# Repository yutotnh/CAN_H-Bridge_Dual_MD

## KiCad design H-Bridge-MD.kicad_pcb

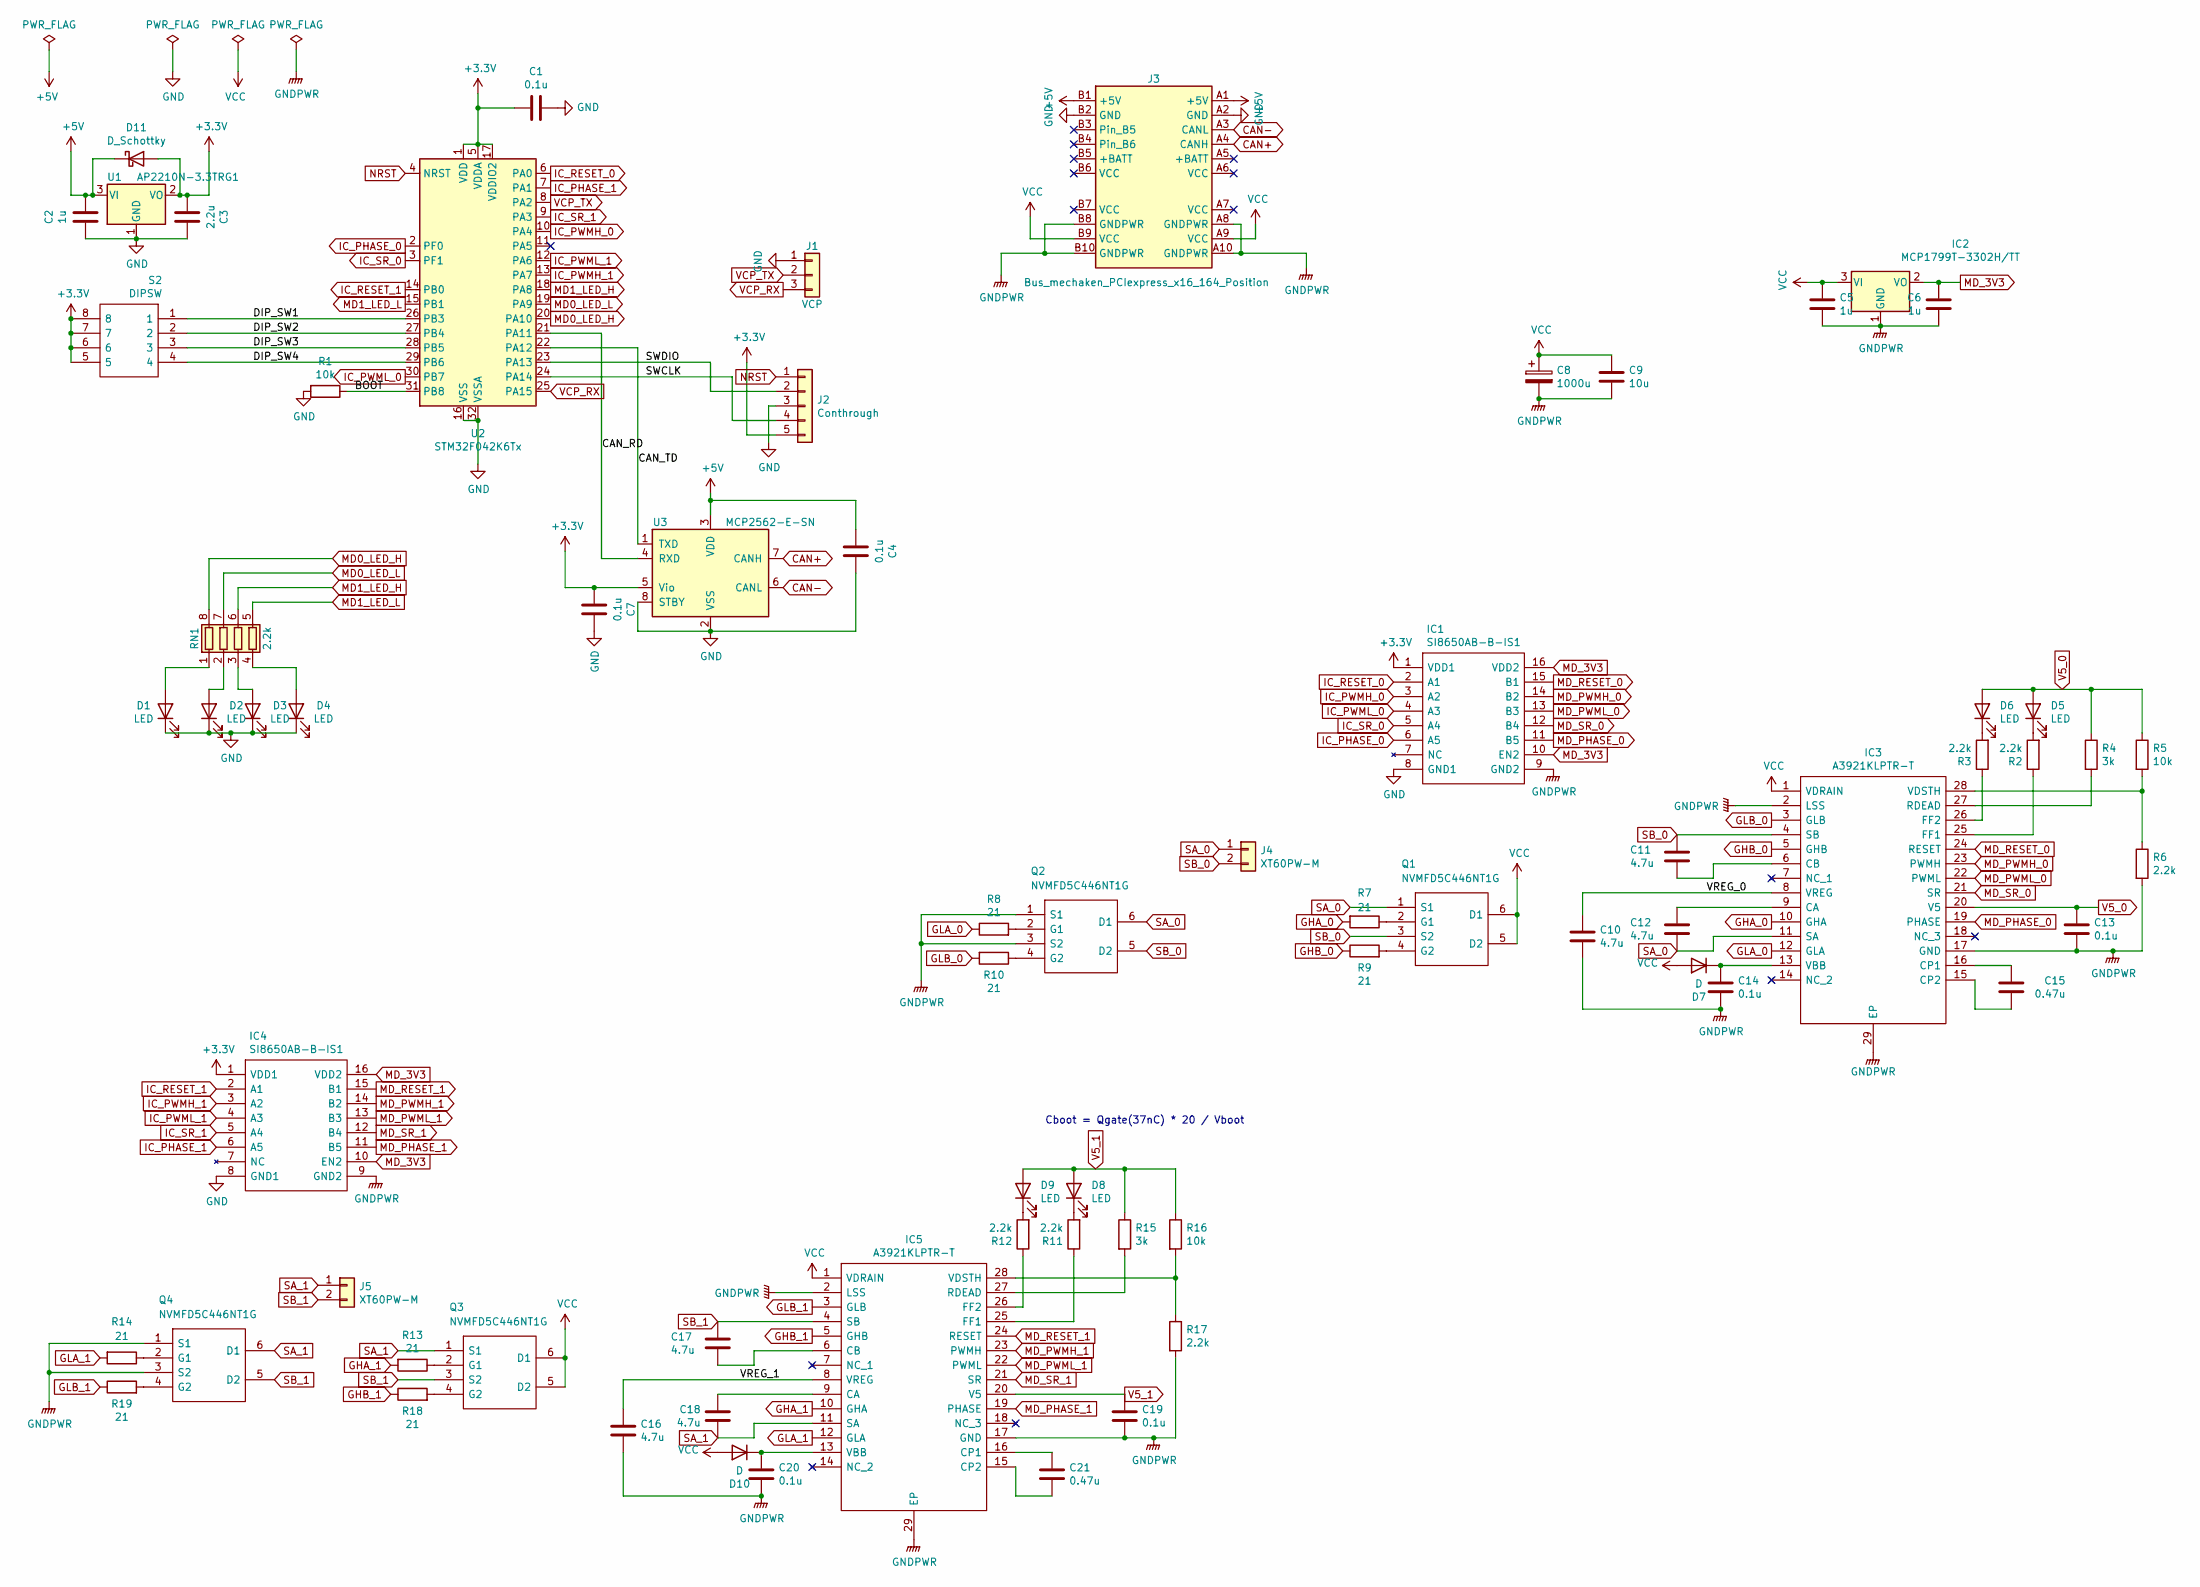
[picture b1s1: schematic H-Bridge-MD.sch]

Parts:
C1, C4, C7, C13, C14, C19, C20: 0.1u; C_0805_2012Metric
C2, C5, C6: 1u; C_0805_2012Metric
C3: 2.2u; C_0805_2012Metric
C8: 1000u; PinSocket_1x02_P2.54mm_Vertical
C9: 10u; C_0805_2012Metric
C10, C11, C12, C16, C17, C18: 4.7u; C_0805_2012Metric
C15, C21: 0.47u; C_0805_2012Metric
D1, D2, D3, D4, D5, D6, D8, D9: LED; LED_0603_1608Metric_Castellated
D7, D10: D; D_0603_1608Metric
D11: D_Schottky; D_0603_1608Metric
IC1, IC4: SI8650AB-B-IS1; SOIC127P600X175-16N; Mouser Part Number 634-SI8650AB-B-IS1
IC2: MCP1799T-3302H/TT; SOT-23_Handsoldering; Manufacturer_Part_Number MCP1799T-3302H/TT
IC3, IC5: A3921KLPTR-T; SOP65P640X120-29N; Manufacturer_Part_Number A3921KLPTR-T
J1: VCP; PinHeader_1x03_P2.54mm_Vertical
J2: Conthrough; PinHeader_1x05_P2.54mm_Vertical
J3: Bus_mechaken_PCIexpress_x16_164_Position; BUS_mechaken_PCIexpress_x16
J4, J5: XT60PW-M; XT60PW
Q1, Q2, Q3, Q4: NVMFD5C446NT1G; NVMFD5C446NLWFT1G; Mouser Part Number 863-NVMFD5C446NT1G
R1, R5, R16: 10k; R_0603_1608Metric
R2, R3, R6, R11, R12, R17: 2.2k; R_0603_1608Metric
R4, R15: 3k; R_0603_1608Metric
R7, R8, R9, R10, R13, R14, R18, R19: 21; R_0603_1608Metric
RN1: 2.2k; R_Array_Convex_4x1206
S2: DIPSW; SW_DIP_SPSTx04_Slide_9.78x12.34mm_W7.62mm_P2.54mm; Manufacturer_Part_Number IKD0403101
U1: AP2210N-3.3TRG1; SOT-23W_Handsoldering
U2: STM32F042K6Tx; LQFP-32_7x7mm_P0.8mm
U3: MCP2562-E-SN; SOIC-8_3.9x4.9mm_P1.27mm

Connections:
+3V3: C1.2, C3.2, C7.2, D11.2 (A), IC1.1 (VDD1), IC4.1 (VDD1), J2.5, S2.5, S2.6, S2.7, S2.8, U1.2 (VO), U2.1 (VDD), U2.5 (VDDA), U2.17 (VDDIO2), U3.5 (Vio)
+5V: C2.1, C4.2, D11.1 (K), J3.A1 (+5V), J3.B1 (+5V), U1.3 (VI), U3.3 (VDD)
/BOOT: R1.1, U2.31 (PB8)
/CAN_RD: U2.21 (PA11), U3.4 (RXD)
/CAN_TD: U2.22 (PA12), U3.1 (TXD)
/DIP_SW1: S2.1, U2.26 (PB3)
/DIP_SW2: S2.2, U2.27 (PB4)
/DIP_SW3: S2.3, U2.28 (PB5)
/DIP_SW4: S2.4, U2.29 (PB6)
/SWCLK: J2.4, U2.24 (PA14)
/SWDIO: J2.2, U2.23 (PA13)
/VREG_0: C10.1, IC3.8 (VREG)
/VREG_1: C16.1, IC5.8 (VREG)
CAN+: J3.A4 (CANH), U3.7 (CANH)
CAN-: J3.A3 (CANL), U3.6 (CANL)
GHA_0: IC3.10 (GHA), R7.2
GHA_1: IC5.10 (GHA), R13.2
GHB_0: IC3.5 (GHB), R9.1
GHB_1: IC5.5 (GHB), R18.1
GLA_0: IC3.12 (GLA), R8.1
GLA_1: IC5.12 (GLA), R14.2
GLB_0: IC3.3 (GLB), R10.2
GLB_1: IC5.3 (GLB), R19.1
GND: C1.1, C2.2, C3.1, C4.1, C7.1, D1.1 (K), D2.1 (K), D3.1 (K), D4.1 (K), IC1.8 (GND1), IC4.8 (GND1), J1.1, J2.3, J3.A2 (GND), J3.B2 (GND), R1.2, U1.1 (GND), U2.16 (VSS), U2.32 (VSSA), U3.2 (VSS), U3.8 (STBY)
GNDPWR: C5.2, C6.1, C8.2, C9.2, C10.2, C13.2, C14.2, C16.2, C19.2, C20.2, IC1.9 (GND2), IC2.1 (GND), IC3.2 (LSS), IC3.17 (GND), IC3.29 (EP), IC4.9 (GND2), IC5.2 (LSS), IC5.17 (GND), IC5.29 (EP), J3.A8 (GNDPWR), J3.A10 (GNDPWR), J3.B8 (GNDPWR), J3.B10 (GNDPWR), Q2.1 (S1), Q2.3 (S2), Q4.1 (S1), Q4.3 (S2), R6.2, R17.2
IC_PHASE_0: IC1.6 (A5), U2.2 (PF0)
IC_PHASE_1: IC4.6 (A5), U2.7 (PA1)
IC_PWMH_0: IC1.3 (A2), U2.10 (PA4)
IC_PWMH_1: IC4.3 (A2), U2.13 (PA7)
IC_PWML_0: IC1.4 (A3), U2.30 (PB7)
IC_PWML_1: IC4.4 (A3), U2.12 (PA6)
IC_RESET_0: IC1.2 (A1), U2.6 (PA0)
IC_RESET_1: IC4.2 (A1), U2.14 (PB0)
IC_SR_0: IC1.5 (A4), U2.3 (PF1)
IC_SR_1: IC4.5 (A4), U2.9 (PA3)
MD0_LED_H: RN1.8 (R1.2), U2.20 (PA10)
MD0_LED_L: RN1.7 (R2.2), U2.19 (PA9)
MD1_LED_H: RN1.6 (R3.2), U2.18 (PA8)
MD1_LED_L: RN1.5 (R4.2), U2.15 (PB1)
MD_3V3: C6.2, IC1.10 (EN2), IC1.16 (VDD2), IC2.2 (VO), IC4.10 (EN2), IC4.16 (VDD2)
MD_PHASE_0: IC1.11 (B5), IC3.19 (PHASE)
MD_PHASE_1: IC4.11 (B5), IC5.19 (PHASE)
MD_PWMH_0: IC1.14 (B2), IC3.23 (PWMH)
MD_PWMH_1: IC4.14 (B2), IC5.23 (PWMH)
MD_PWML_0: IC1.13 (B3), IC3.22 (PWML)
MD_PWML_1: IC4.13 (B3), IC5.22 (PWML)
MD_RESET_0: IC1.15 (B1), IC3.24 (RESET)
MD_RESET_1: IC4.15 (B1), IC5.24 (RESET)
MD_SR_0: IC1.12 (B4), IC3.21 (SR)
MD_SR_1: IC4.12 (B4), IC5.21 (SR)
NRST: J2.1, U2.4 (NRST)
unnamed: C11.2, IC3.6 (CB)
unnamed: C12.1, IC3.9 (CA)
unnamed: C14.1, D7.1 (K), IC3.13 (VBB)
unnamed: C15.1, IC3.15 (CP2)
unnamed: C15.2, IC3.16 (CP1)
unnamed: C17.2, IC5.6 (CB)
unnamed: C18.2, IC5.9 (CA)
unnamed: C20.1, D10.1 (K), IC5.13 (VBB)
unnamed: C21.1, IC5.15 (CP2)
unnamed: C21.2, IC5.16 (CP1)
unnamed: D1.2 (A), RN1.1 (R1.1)
unnamed: D2.2 (A), RN1.2 (R2.1)
unnamed: D3.2 (A), RN1.3 (R3.1)
unnamed: D4.2 (A), RN1.4 (R4.1)
unnamed: D5.1 (K), R2.2
unnamed: D6.1 (K), R3.2
unnamed: D8.1 (K), R11.2
unnamed: D9.1 (K), R12.2
unnamed: IC3.25 (FF1), R2.1
unnamed: IC3.26 (FF2), R3.1
unnamed: IC3.27 (RDEAD), R4.2
unnamed: IC3.28 (VDSTH), R5.2, R6.1
unnamed: IC5.25 (FF1), R11.1
unnamed: IC5.26 (FF2), R12.1
unnamed: IC5.27 (RDEAD), R15.2
unnamed: IC5.28 (VDSTH), R16.2, R17.1
unnamed: Q1.2 (G1), R7.1
unnamed: Q1.4 (G2), R9.2
unnamed: Q2.2 (G1), R8.2
unnamed: Q2.4 (G2), R10.1
unnamed: Q3.2 (G1), R13.1
unnamed: Q3.4 (G2), R18.2
unnamed: Q4.2 (G1), R14.1
unnamed: Q4.4 (G2), R19.2
SA_0: C12.2, IC3.11 (SA), J4.1, Q1.1 (S1), Q2.6 (D1)
SA_1: C18.1, IC5.11 (SA), J5.1, Q3.1 (S1), Q4.6 (D1)
SB_0: C11.1, IC3.4 (SB), J4.2, Q1.3 (S2), Q2.5 (D2)
SB_1: C17.1, IC5.4 (SB), J5.2, Q3.3 (S2), Q4.5 (D2)
V5_0: C13.1, D5.2 (A), D6.2 (A), IC3.20 (V5), R4.1, R5.1
V5_1: C19.1, D8.2 (A), D9.2 (A), IC5.20 (V5), R15.1, R16.1
VCC: C5.1, C8.1, C9.1, D7.2 (A), D10.2 (A), IC2.3 (VI), IC3.1 (VDRAIN), IC5.1 (VDRAIN), J3.A9 (VCC), J3.B9 (VCC), Q1.5 (D2), Q1.6 (D1), Q3.5 (D2), Q3.6 (D1)
VCP_RX: J1.3, U2.25 (PA15)
VCP_TX: J1.2, U2.8 (PA2)

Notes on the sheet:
Cboot = Qgate(37nC) * 20 / Vboot

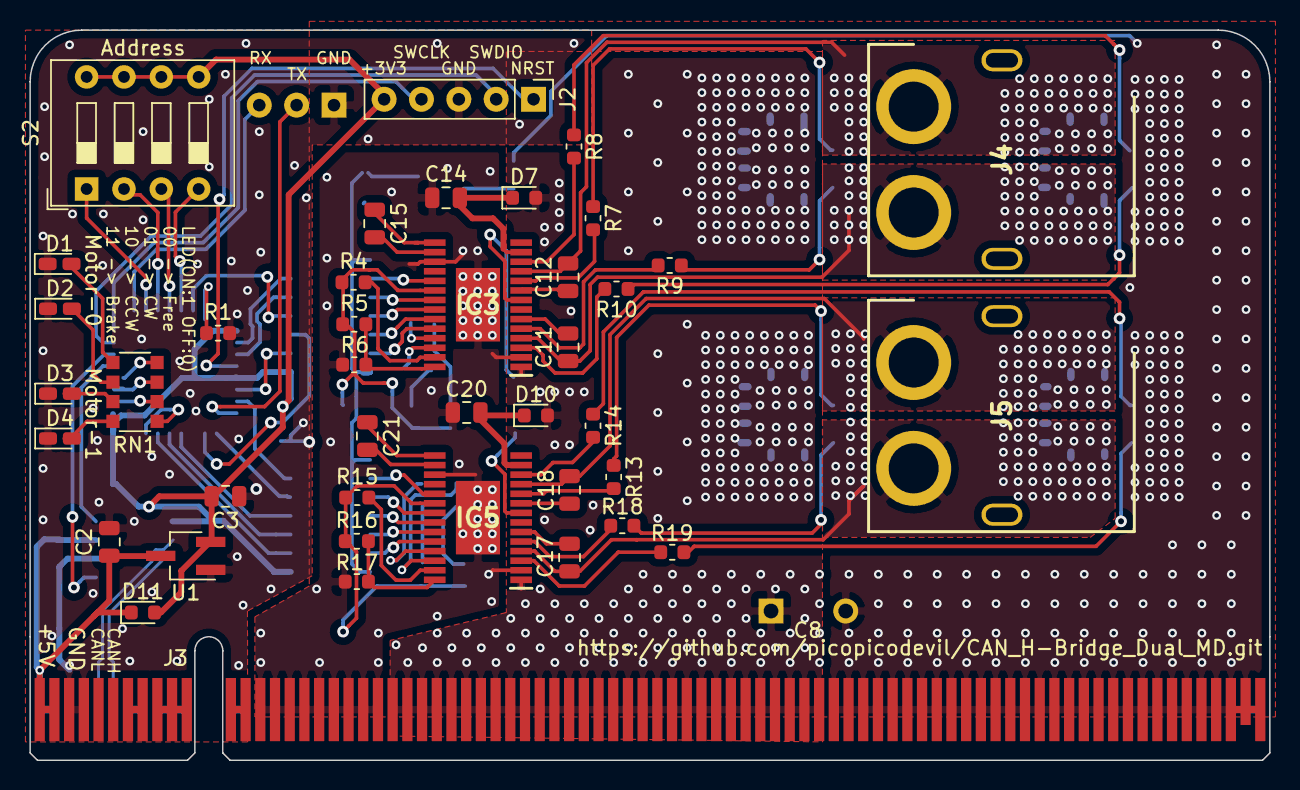
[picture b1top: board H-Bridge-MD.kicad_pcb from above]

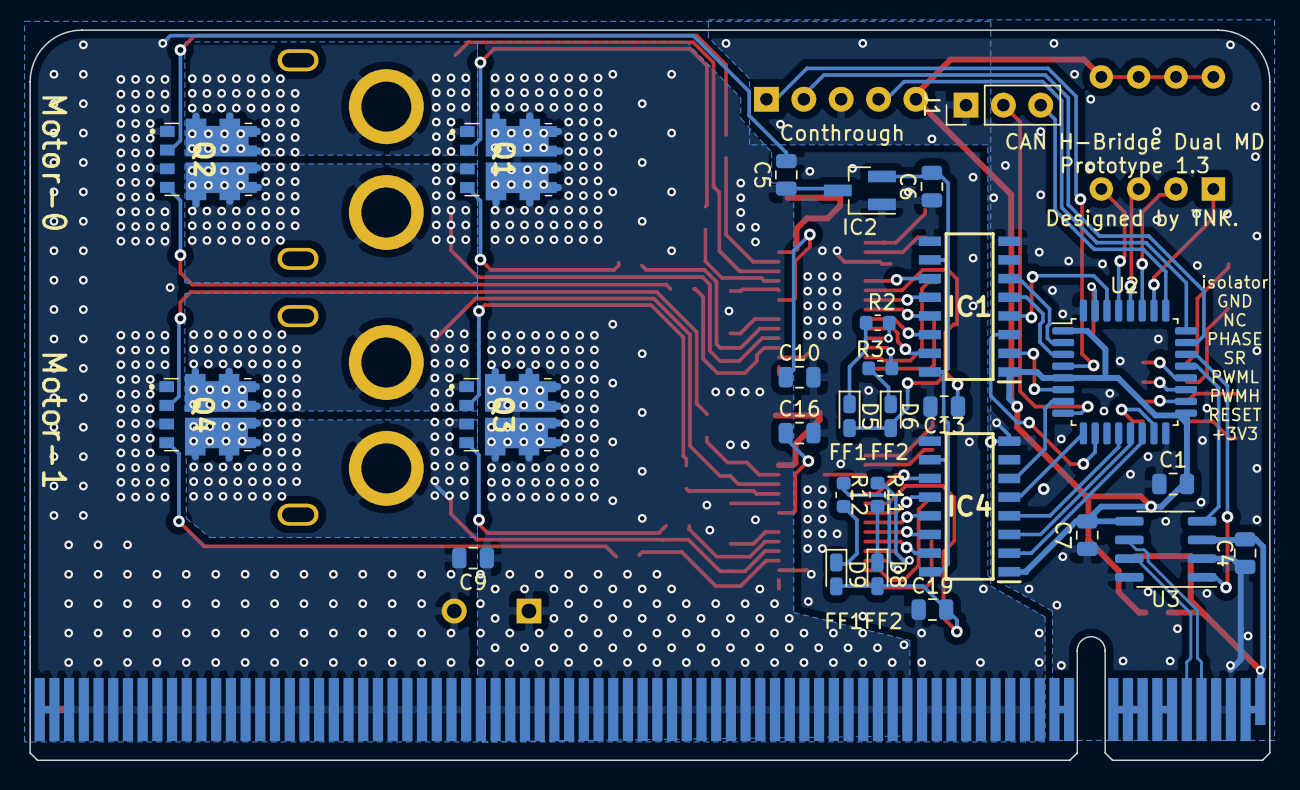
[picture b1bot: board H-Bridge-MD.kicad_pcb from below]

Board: 2 copper layers, 84.3 x 49.7 mm, 70 parts (29 on the bottom side), 94 nets.

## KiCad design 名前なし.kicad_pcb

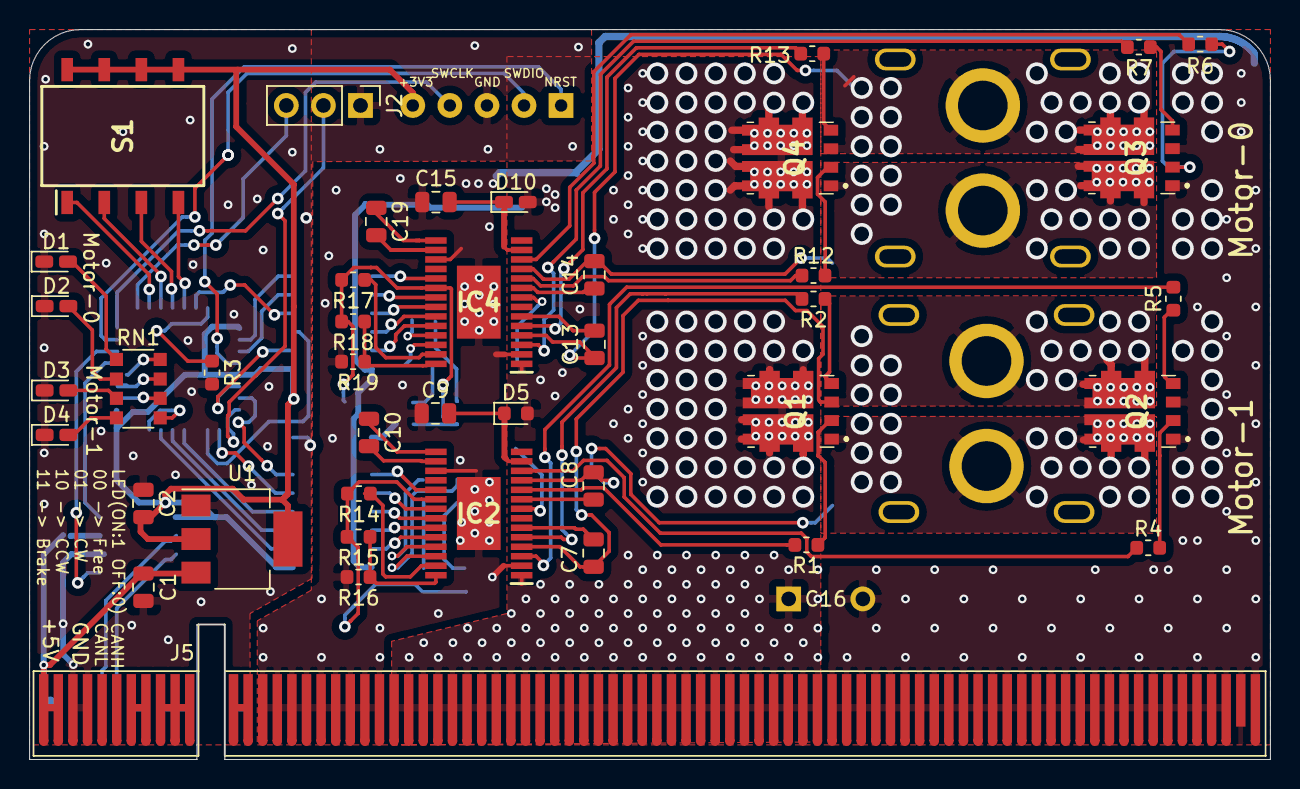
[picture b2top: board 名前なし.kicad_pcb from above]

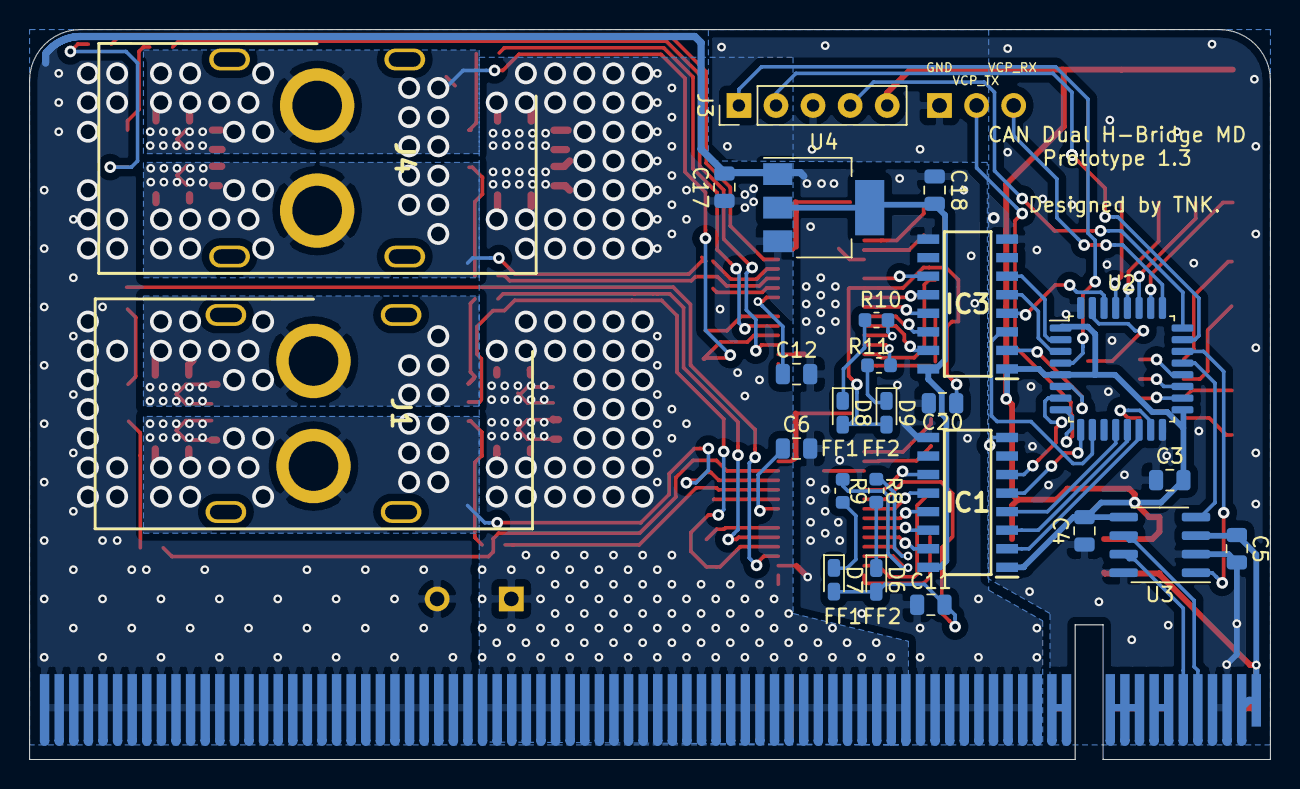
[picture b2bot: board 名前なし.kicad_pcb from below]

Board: 2 copper layers, 85.0 x 50.0 mm, 68 parts (25 on the bottom side), 94 nets.

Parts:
C1: 1u; C_0805_2012Metric
C2, C6, C7, C8, C13, C14: 4.7u; C_0805_2012Metric
C3, C4, C5, C9, C11, C15: 0.1u; C_0805_2012Metric
C10, C19: 0.47u; C_0805_2012Metric
C12, C18: 4.7uF; C_0805_2012Metric
C16: 1000u; PinSocket_1x02_P2.54mm_Vertical
C17: 1uF; C_0805_2012Metric
C20: 0.1uF; C_0805_2012Metric
D1, D2, D3, D4, D6, D7, D8, D9: LED; LED_0603_1608Metric_Castellated
D5: D; D_0603_1608Metric
D10: D; LED_0603_1608Metric_Castellated
IC1, IC3: SI8650AB-B-IS1; SOIC127P600X175-16N
IC2, IC4: A3921KLPTR-T; SOP65P640X120-29N
J1, J4: Conn_01x02; XT60PW_Reversible
J2: Conn_01x03; PinHeader_1x03_P2.54mm_Vertical
J3: Conn_01x05; PinHeader_1x05_P2.54mm_Vertical
J5: Bus_mechaken_PCIexpress_x16_164_Position; BUS_mechaken_PCIexpress_x16_164_Position
Q1, Q2, Q3, Q4: NVMFD5C446NT1G; NVMFD5C446NLWFT1G
R1, R2, R4, R5, R6, R7, R12, R13: 21; R_0603_1608Metric
R3: 10k; R_0603_1608Metric
R8, R9, R10, R11: 2.2k; R_0603_1608Metric
R14, R17: 3k; R_0603_1608Metric
R15, R18: 3.74k; R_0603_1608Metric
R16, R19: 1.2k; R_0603_1608Metric
RN1: 2.2k; R_Array_Convex_4x1206
S1: IKD0403101; SOP254P980X370-8N
U1: LDL1117S33R_SOT223-4; SOT-223-3_TabPin2
U2: STM32F042K6Tx; LQFP-32_7x7mm_P0.8mm
U3: MCP2562-E-SN; SOIC-8_3.9x4.9mm_P1.27mm
U4: LDL1117S33TR_SOT223-4; SOT-223-3_TabPin2

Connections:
+3V3: C2.2, C3.2, C4.2, IC1.1, IC3.1, J3.5, S1.5, S1.6, S1.7, S1.8, U1.2, U2.1, U2.5, U2.17, U3.5
+5V: C1.1, C5.2, J5.A1, J5.B1, U1.3, U3.3
/BOOT: R3.1, U2.31
/CAN_RD: U2.21, U3.4
/CAN_TD: U2.22, U3.1
/SWCLK: J3.4, U2.24
/SWDIO: J3.2, U2.23
CAN+: J5.A4, U3.7
CAN-: J5.A3, U3.6
DIP_SW_1: S1.1, U2.26
DIP_SW_2: S1.2, U2.27
DIP_SW_3: S1.3, U2.28
DIP_SW_4: S1.4, U2.29
GHA_0: IC4.10, R12.1
GHA_1: IC2.10, R1.1
GHB_0: IC4.5, R13.2
GHB_1: IC2.5, R2.2
GLA_0: IC4.12, R6.1
GLA_1: IC2.12, R4.1
GLB_0: IC4.3, R7.2
GLB_1: IC2.3, R5.2
GND: C1.2, C2.1, C3.1, C4.1, C5.1, D1.1, D2.1, D3.1, D4.1, IC1.8, IC3.8, J2.1, J3.3, J5.A2, J5.B2, R3.2, U1.1, U2.16, U2.32, U3.2, U3.8
GNDPWR: C6.2, C9.2, C11.2, C12.2, C15.2, C16.2, C17.2, C18.1, C20.2, IC1.9, IC2.2, IC2.17, IC2.29, IC3.9, IC4.2, IC4.17, IC4.29, J5.A8, J5.A10, J5.B8, J5.B10, Q2.1, Q2.3, Q3.1, Q3.3, R16.2, R19.2, U4.1
IC_PHASE_0: IC3.6, U2.2
IC_PHASE_1: IC1.6, U2.7
IC_PWMH_0: IC3.3, U2.10
IC_PWMH_1: IC1.3, U2.13
IC_PWML_0: IC3.4, U2.30
IC_PWML_1: IC1.4, U2.12
IC_RESET_0: IC3.2, U2.6
IC_RESET_1: IC1.2, U2.14
IC_SR_0: IC3.5, U2.3
IC_SR_1: IC1.5, U2.9
MD0_LED_H: RN1.8, U2.20
MD0_LED_L: RN1.7, U2.19
MD1_LED_H: RN1.6, U2.18
MD1_LED_L: RN1.5, U2.15
MD_3V3: C18.2, IC1.16, IC3.16, U4.2
MD_FF1_0: IC4.25, R10.1
MD_FF1_1: IC2.26, R9.1
MD_FF2_0: IC4.26, R11.1
MD_FF2_1: IC2.25, R8.1
MD_PHASE_0: IC3.11, IC4.19
MD_PHASE_1: IC1.11, IC2.19
MD_PWMH_0: IC3.14, IC4.23
MD_PWMH_1: IC1.14, IC2.23
MD_PWML_0: IC3.13, IC4.22
MD_PWML_1: IC1.13, IC2.22
MD_RESET_0: IC3.15, IC4.24
MD_RESET_1: IC1.15, IC2.24
MD_SR_0: IC3.12, IC4.21
MD_SR_1: IC1.12, IC2.21
NRST: J3.1, U2.4
unnamed: C7.2, IC2.6
unnamed: C8.2, IC2.9
unnamed: C9.1, D5.1, IC2.13
unnamed: C10.1, IC2.15
unnamed: C10.2, IC2.16
unnamed: C13.2, IC4.6
unnamed: C14.1, IC4.9
unnamed: C15.1, D10.1, IC4.13
unnamed: C19.1, IC4.15
unnamed: C19.2, IC4.16
unnamed: D1.2, RN1.1
unnamed: D2.2, RN1.2
unnamed: D3.2, RN1.3
unnamed: D4.2, RN1.4
unnamed: D6.1, R8.2
unnamed: D7.1, R9.2
unnamed: D8.1, R10.2
unnamed: D9.1, R11.2
unnamed: IC2.27, R14.1
unnamed: IC2.28, R15.1, R16.1
unnamed: IC4.27, R17.1
unnamed: IC4.28, R18.1, R19.1
unnamed: Q1.2, R1.2
unnamed: Q1.4, R2.1
unnamed: Q2.2, R4.2
unnamed: Q2.4, R5.1
unnamed: Q3.2, R6.2
unnamed: Q3.4, R7.1
unnamed: Q4.2, R12.2
unnamed: Q4.4, R13.1
SA_0: C14.2, IC4.11, J4.2, Q3.6, Q4.1
SA_1: C8.1, IC2.11, J1.2, Q1.1, Q2.6
SB_0: C13.1, IC4.4, J4.1, Q3.5, Q4.3
SB_1: C7.1, IC2.4, J1.1, Q1.3, Q2.5
V5_0: C20.1, D8.2, D9.2, IC4.20, R17.2, R18.2
V5_1: C11.1, D6.2, D7.2, IC2.20, R14.2, R15.2
VCC: C16.1, C17.1, D5.2, D10.2, IC2.1, IC4.1, J5.A9, J5.B9, Q1.5, Q1.6, Q4.5, Q4.6, U4.3
VCP_RX: J2.3, U2.25
VCP_TX: J2.2, U2.8
VREG_0: C12.1, IC4.8
VREG_1: C6.1, IC2.8

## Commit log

2019-11-19 Prototype 1.0
2019-11-19 Prototype 1.1
    change 3.3V regulator & thermal via
2019-12-03 Prototype1.2
    Change: ST-LINK Conn, Rgs, Rg
2019-12-04 Prototype1.3
    Change LDO, 0.47uF size
    Correction ST-LINK foot-print
2019-12-07 update
    軽微な配線の修正
2019-12-07 clean
2019-12-10 remove RESET_SW
2019-12-10 Fix FET via
2019-12-11 add 3V3LDO & pad
2019-12-12 Prototype 1.3
    FusionPCB(12/12)
2019-12-16 change
    Bootstrap Capacitor 0.1uF -> 4.4uF
2019-12-17 fix bootstrap capacitor
2019-12-18 update
    change MD name
2019-12-18 update
    update name
2019-12-27 fix
    FF1&FF2 LED
2019-12-27 fix
    Pcbnewのファイルが見れない問題を修正
2020-01-06 change
    書き込み用のピンをコンスルー対応に変更
2020-01-06 change
    抵抗アレイを1206に変更
2020-01-06 change
    ダイオードのフットプリントをハーフホール向けに変更
    その他の微修正（主に配線）
2020-01-07 change
    電解コンデンサを搭載できるように配置を大幅変更
2020-01-07 change
    シルクを少し変更
2020-01-08 change
    放熱ビアを1mmに変更
    その他大幅な変更
2020-01-10 change
    4pinのDIPスイッチを追加
2020-01-11 change
    FET等の裏表反転
2020-01-12 change
    電源部のパスコンの追加
2020-01-12 fix
    Motor0側にあるA3921のVCCにつながるビアを増加
2020-01-18 change LDO
    アイソレータ用のLDOを変更
2020-01-19 change
    エッジコネクタ（PCIe）を公式のライブラリを基にしたフットプリントに変更
2020-01-27 fix
    細かな修正
2020-01-28 error
2020-01-28 delete file
    X220で生成されてしまったファイルを削除
2020-02-15 change
    check to elecrow
2020-02-16 change
    3Dデータを関連付け
2020-02-16 add
    step file
2020-02-17 clean
    シルクを修正
2020-02-17 change
    Si8650のEN2ピンに3.3Vを供給するように変更
2020-02-21 add
    LDOの逆電圧防止用のSBDを追加
2020-02-21 fix
    配線のエラーを修正
2020-02-21 change
    コンスルーの3Dデータ（ピンヘッダ）を消去
2020-02-22 clean
    回路図の配線をわかりやすいように修正
2020-02-24 change
    XT60の向きを固定
2020-02-25 change
    許容電流を上げた
2020-02-25 change
    電解コンデンサの位置を修正
2020-02-28 fix
    Hブリッジのゾーンを修正
2020-03-01 fix
    モーターへの配線を容易に行えるよう修正
2020-03-04 clean
    ガーバーデータを出力
2020-06-21 Release
    Release Prototype-1.3
2020-06-21 add
    gitignoreを追加
2020-06-21 .gitignore is now working
2021-09-21 Update: USB TX RXをコンスルーに対応
2021-09-21 Remove: 不要なファイルを削除
2021-09-21 Update: SI8650用の3Dモデルのパスを追加
2021-09-24 Create LICENSE
